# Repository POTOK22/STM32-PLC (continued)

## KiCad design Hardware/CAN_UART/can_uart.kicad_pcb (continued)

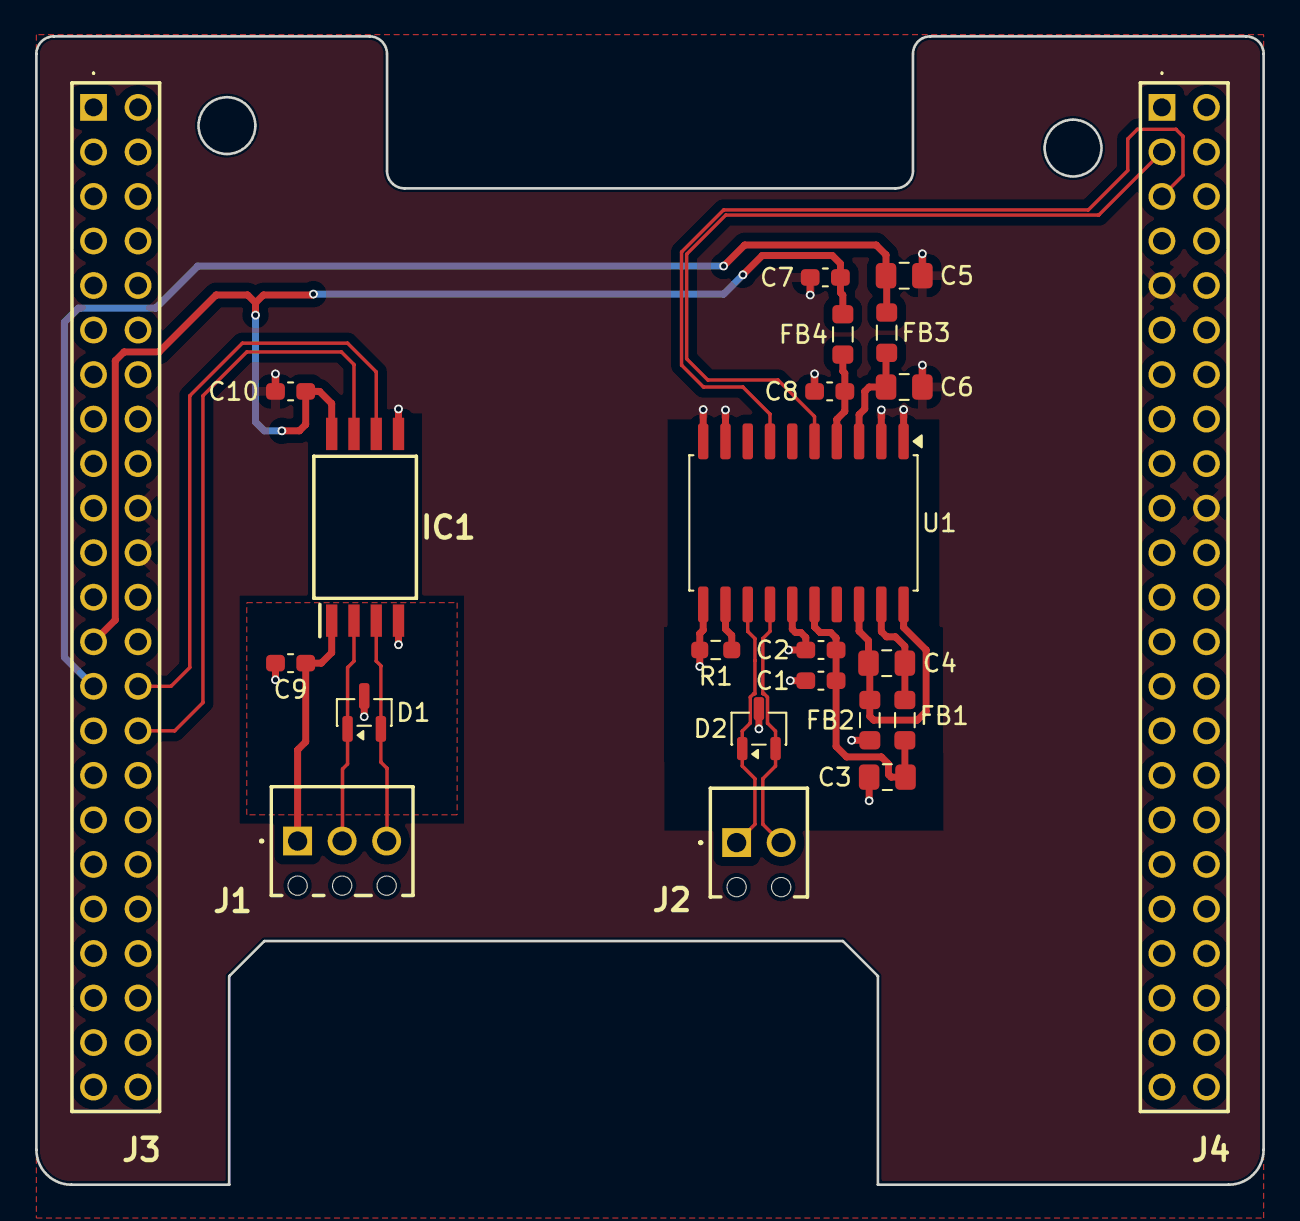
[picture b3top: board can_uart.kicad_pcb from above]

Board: 4 copper layers, 70.0 x 65.5 mm, 23 parts (0 on the bottom side), 20 nets.

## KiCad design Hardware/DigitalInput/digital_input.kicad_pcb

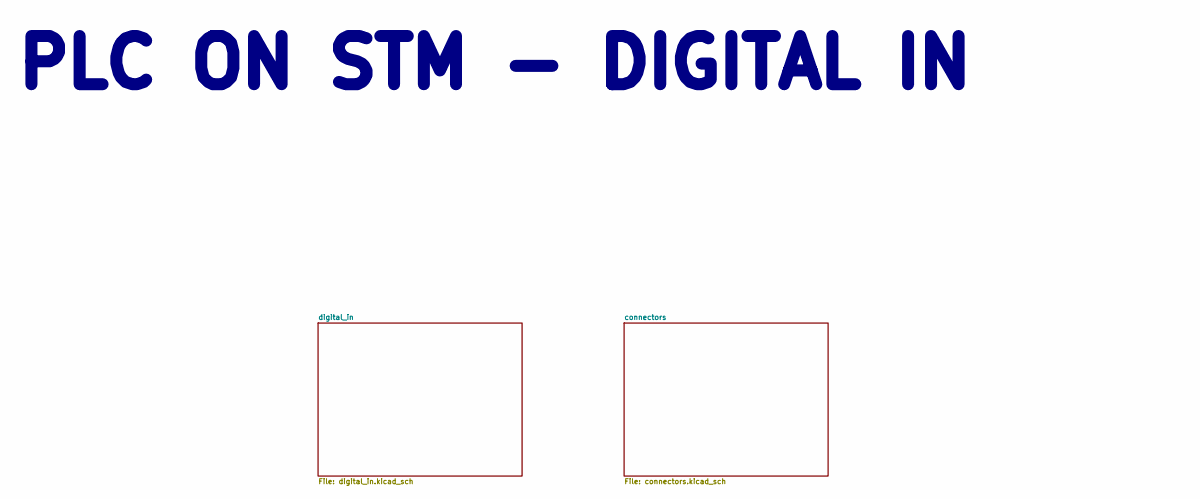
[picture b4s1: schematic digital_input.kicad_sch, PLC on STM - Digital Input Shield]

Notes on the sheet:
PLC ON STM - DIGITAL IN

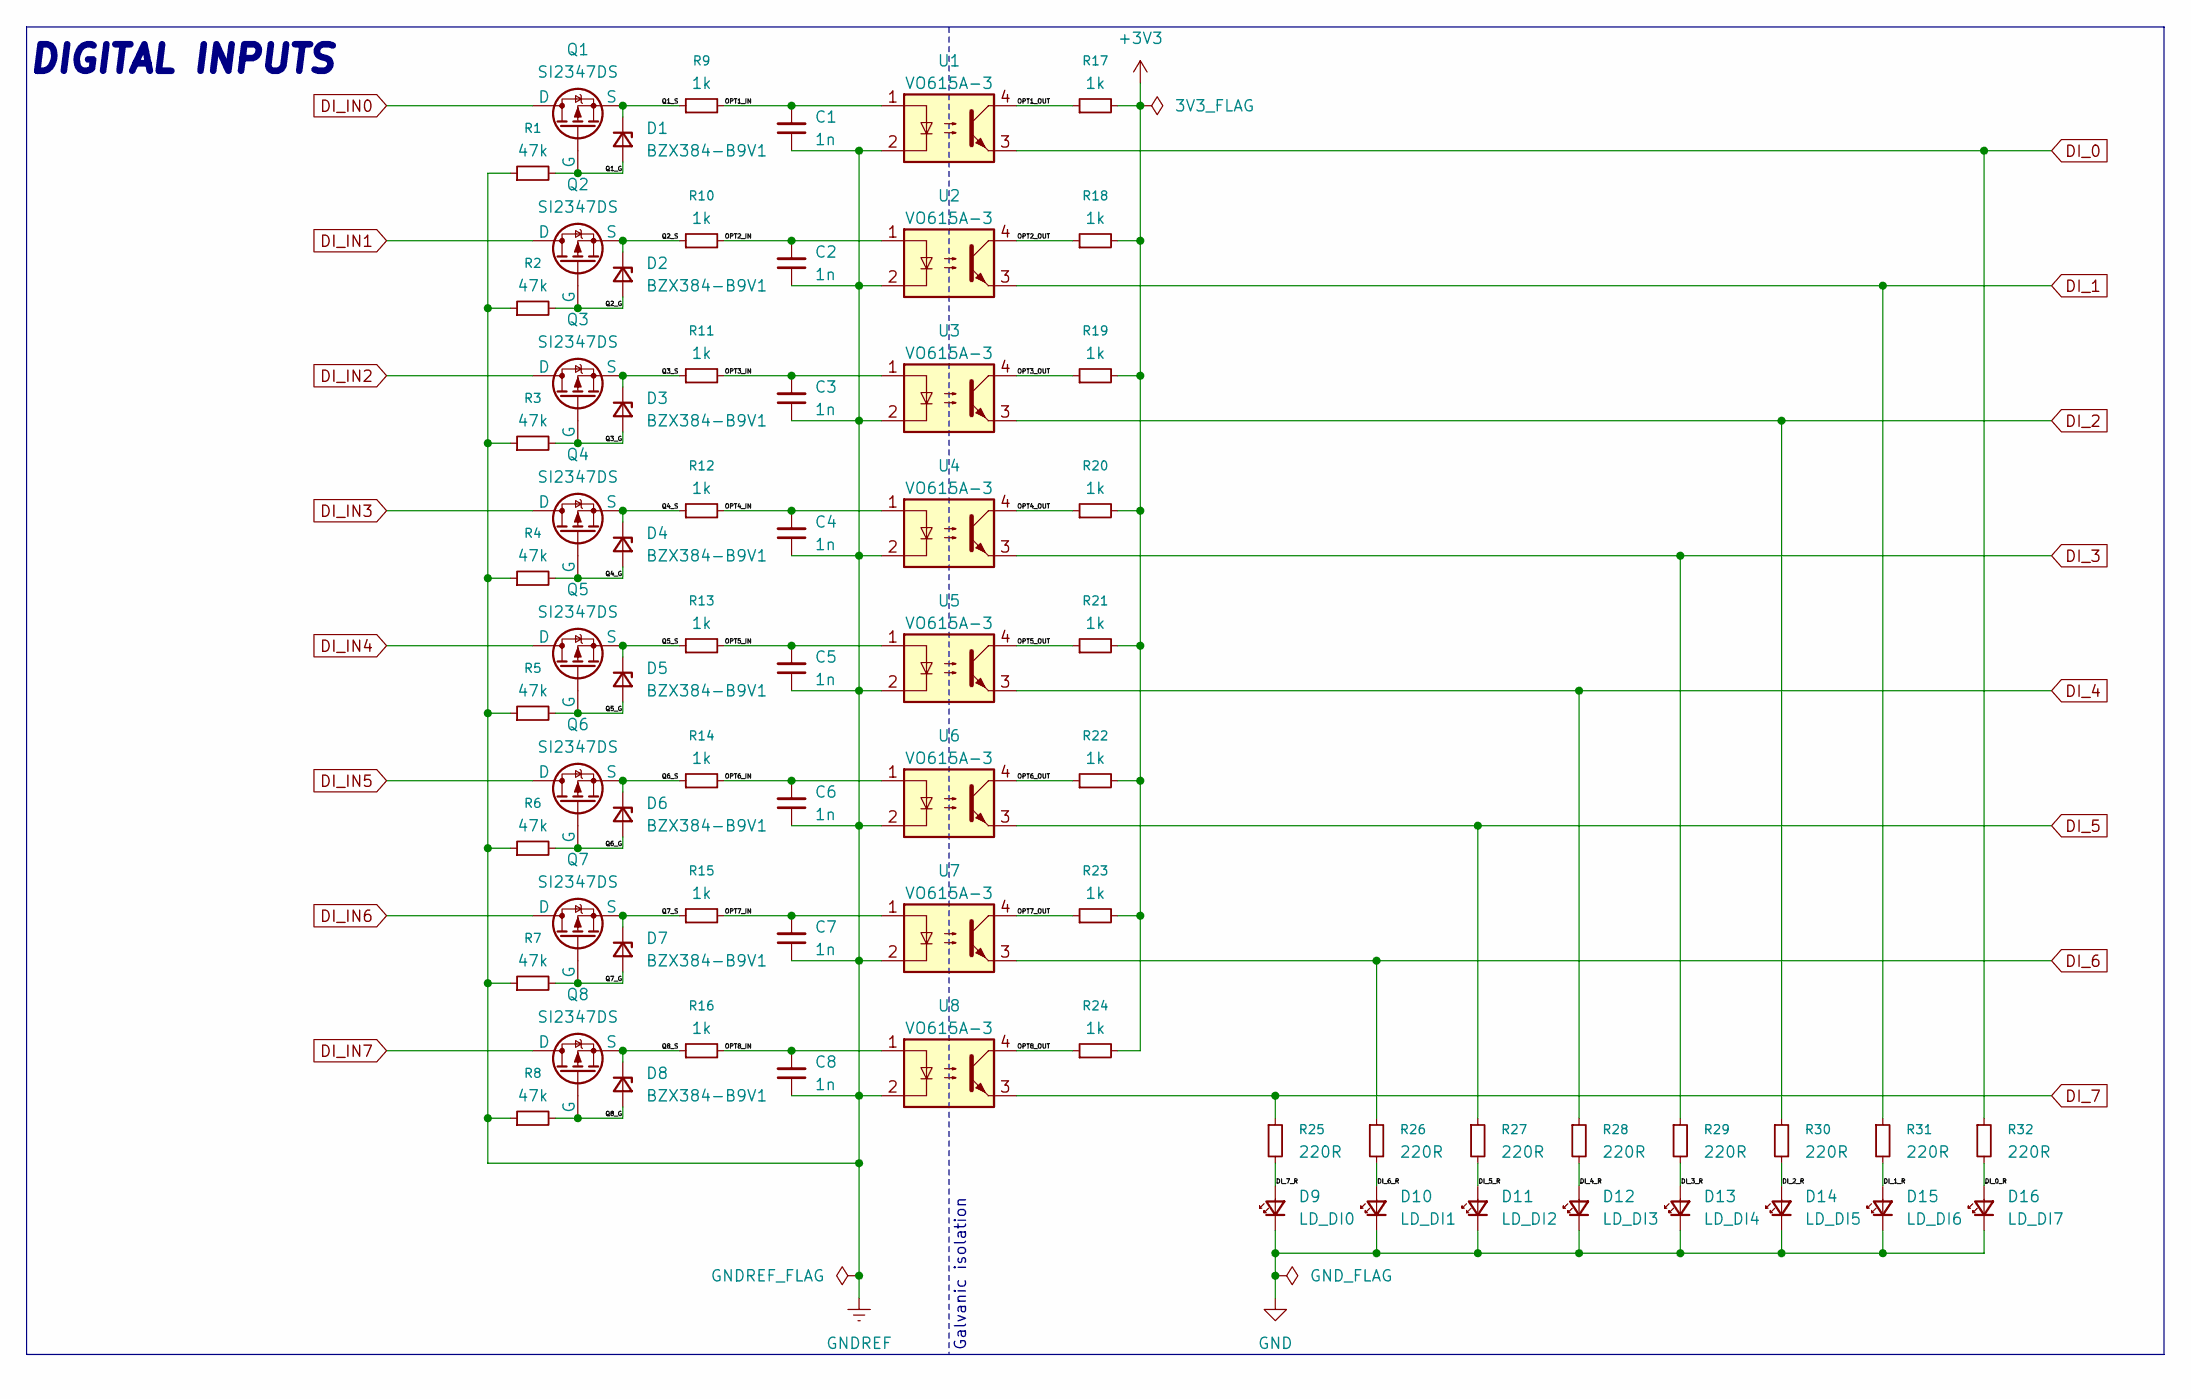
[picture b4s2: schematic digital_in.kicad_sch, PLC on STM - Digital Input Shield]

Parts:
C1, C2, C3, C4, C5, C6, C7, C8: 1n; C_0603_1608Metric_Pad1.08x0.95mm_HandSolder; Mouser Part Number 81-GRT1885C1E102JA2D
D1, D2, D3, D4, D5, D6, D7, D8: BZX384-B9V1; D_SOD-323_HandSoldering; Mouser Part Number 771-BZX384-B9V1-T/R
D9: LD_DI0; LED_0603_1608Metric_Pad1.05x0.95mm_HandSolder
D10: LD_DI1; LED_0603_1608Metric_Pad1.05x0.95mm_HandSolder
D11: LD_DI2; LED_0603_1608Metric_Pad1.05x0.95mm_HandSolder
D12: LD_DI3; LED_0603_1608Metric_Pad1.05x0.95mm_HandSolder
D13: LD_DI4; LED_0603_1608Metric_Pad1.05x0.95mm_HandSolder
D14: LD_DI5; LED_0603_1608Metric_Pad1.05x0.95mm_HandSolder
D15: LD_DI6; LED_0603_1608Metric_Pad1.05x0.95mm_HandSolder
D16: LD_DI7; LED_0603_1608Metric_Pad1.05x0.95mm_HandSolder
Q1, Q2, Q3, Q4, Q5, Q6, Q7, Q8: SI2347DS; SOT-23-3; Mouser Part Number 78-SI2347DS-T1-GE3
R1, R2, R3, R4, R5, R6, R7, R8: 47k; R_0603_1608Metric_Pad0.98x0.95mm_HandSolder; Mouser Part Number 71-CRCW0603-47K-E3
R9, R10, R11, R12, R13, R14, R15, R16, R17, R18, R19, R20, R21, R22, R23, R24: 1k; R_0603_1608Metric_Pad0.98x0.95mm_HandSolder; Mouser Part Number 71-CRCW06031K00FKED
R25, R26, R27, R28, R29, R30, R31, R32: 220R; R_0603_1608Metric_Pad0.98x0.95mm_HandSolder; Mouser Part Number 71-CRCW0603220RFKEAH
U1, U2, U3, U4, U5, U6, U7, U8: VO615A-3; DIP-4_W8.89mm_SMDSocket_LongPads

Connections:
+3V3: R17.2, R18.2, R19.2, R20.2, R21.2, R22.2, R23.2, R24.2; also elsewhere on the board
/digital_in/DI_0_R: D16.2 (A), R32.2
/digital_in/DI_1_R: D15.2 (A), R31.2
/digital_in/DI_2_R: D14.2 (A), R30.2
/digital_in/DI_3_R: D13.2 (A), R29.2
/digital_in/DI_4_R: D12.2 (A), R28.2
/digital_in/DI_5_R: D11.2 (A), R27.2
/digital_in/DI_6_R: D10.2 (A), R26.2
/digital_in/DI_7_R: D9.2 (A), R25.2
/digital_in/OPT1_IN: C1.2, R9.2, U1.1
/digital_in/OPT1_OUT: R17.1, U1.4
/digital_in/OPT2_IN: C2.2, R10.2, U2.1
/digital_in/OPT2_OUT: R18.1, U2.4
/digital_in/OPT3_IN: C3.2, R11.2, U3.1
/digital_in/OPT3_OUT: R19.1, U3.4
/digital_in/OPT4_IN: C4.2, R12.2, U4.1
/digital_in/OPT4_OUT: R20.1, U4.4
/digital_in/OPT5_IN: C5.2, R13.2, U5.1
/digital_in/OPT5_OUT: R21.1, U5.4
/digital_in/OPT6_IN: C6.2, R14.2, U6.1
/digital_in/OPT6_OUT: R22.1, U6.4
/digital_in/OPT7_IN: C7.2, R15.2, U7.1
/digital_in/OPT7_OUT: R23.1, U7.4
/digital_in/OPT8_IN: C8.2, R16.2, U8.1
/digital_in/OPT8_OUT: R24.1, U8.4
/digital_in/Q1_G: D1.2 (A), Q1.2 (G), R1.2
/digital_in/Q1_S: D1.1 (K), Q1.3 (S), R9.1
/digital_in/Q2_G: D2.2 (A), Q2.2 (G), R2.2
/digital_in/Q2_S: D2.1 (K), Q2.3 (S), R10.1
/digital_in/Q3_G: D3.2 (A), Q3.2 (G), R3.2
/digital_in/Q3_S: D3.1 (K), Q3.3 (S), R11.1
/digital_in/Q4_G: D4.2 (A), Q4.2 (G), R4.2
/digital_in/Q4_S: D4.1 (K), Q4.3 (S), R12.1
/digital_in/Q5_G: D5.2 (A), Q5.2 (G), R5.2
/digital_in/Q5_S: D5.1 (K), Q5.3 (S), R13.1
/digital_in/Q6_G: D6.2 (A), Q6.2 (G), R6.2
/digital_in/Q6_S: D6.1 (K), Q6.3 (S), R14.1
/digital_in/Q7_G: D7.2 (A), Q7.2 (G), R7.2
/digital_in/Q7_S: D7.1 (K), Q7.3 (S), R15.1
/digital_in/Q8_G: D8.2 (A), Q8.2 (G), R8.2
/digital_in/Q8_S: D8.1 (K), Q8.3 (S), R16.1
DI_0: R32.1, U1.3; also elsewhere on the board
DI_1: R31.1, U2.3; also elsewhere on the board
DI_2: R30.1, U3.3; also elsewhere on the board
DI_3: R29.1, U4.3; also elsewhere on the board
DI_4: R28.1, U5.3; also elsewhere on the board
DI_5: R27.1, U6.3; also elsewhere on the board
DI_6: R26.1, U7.3; also elsewhere on the board
DI_7: R25.1, U8.3; also elsewhere on the board
DI_IN0: Q1.1 (D); also elsewhere on the board
DI_IN1: Q2.1 (D); also elsewhere on the board
DI_IN2: Q3.1 (D); also elsewhere on the board
DI_IN3: Q4.1 (D); also elsewhere on the board
DI_IN4: Q5.1 (D); also elsewhere on the board
DI_IN5: Q6.1 (D); also elsewhere on the board
DI_IN6: Q7.1 (D); also elsewhere on the board
DI_IN7: Q8.1 (D); also elsewhere on the board
GND: D9.1 (K), D10.1 (K), D11.1 (K), D12.1 (K), D13.1 (K), D14.1 (K), D15.1 (K), D16.1 (K); also elsewhere on the board
GNDREF: C1.1, C2.1, C3.1, C4.1, C5.1, C6.1, C7.1, C8.1, R1.1, R2.1, R3.1, R4.1, R5.1, R6.1, R7.1, R8.1, U1.2, U2.2, U3.2, U4.2, U5.2, U6.2, U7.2, U8.2; also elsewhere on the board

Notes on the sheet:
DIGITAL INPUTS
Galvanic isolation

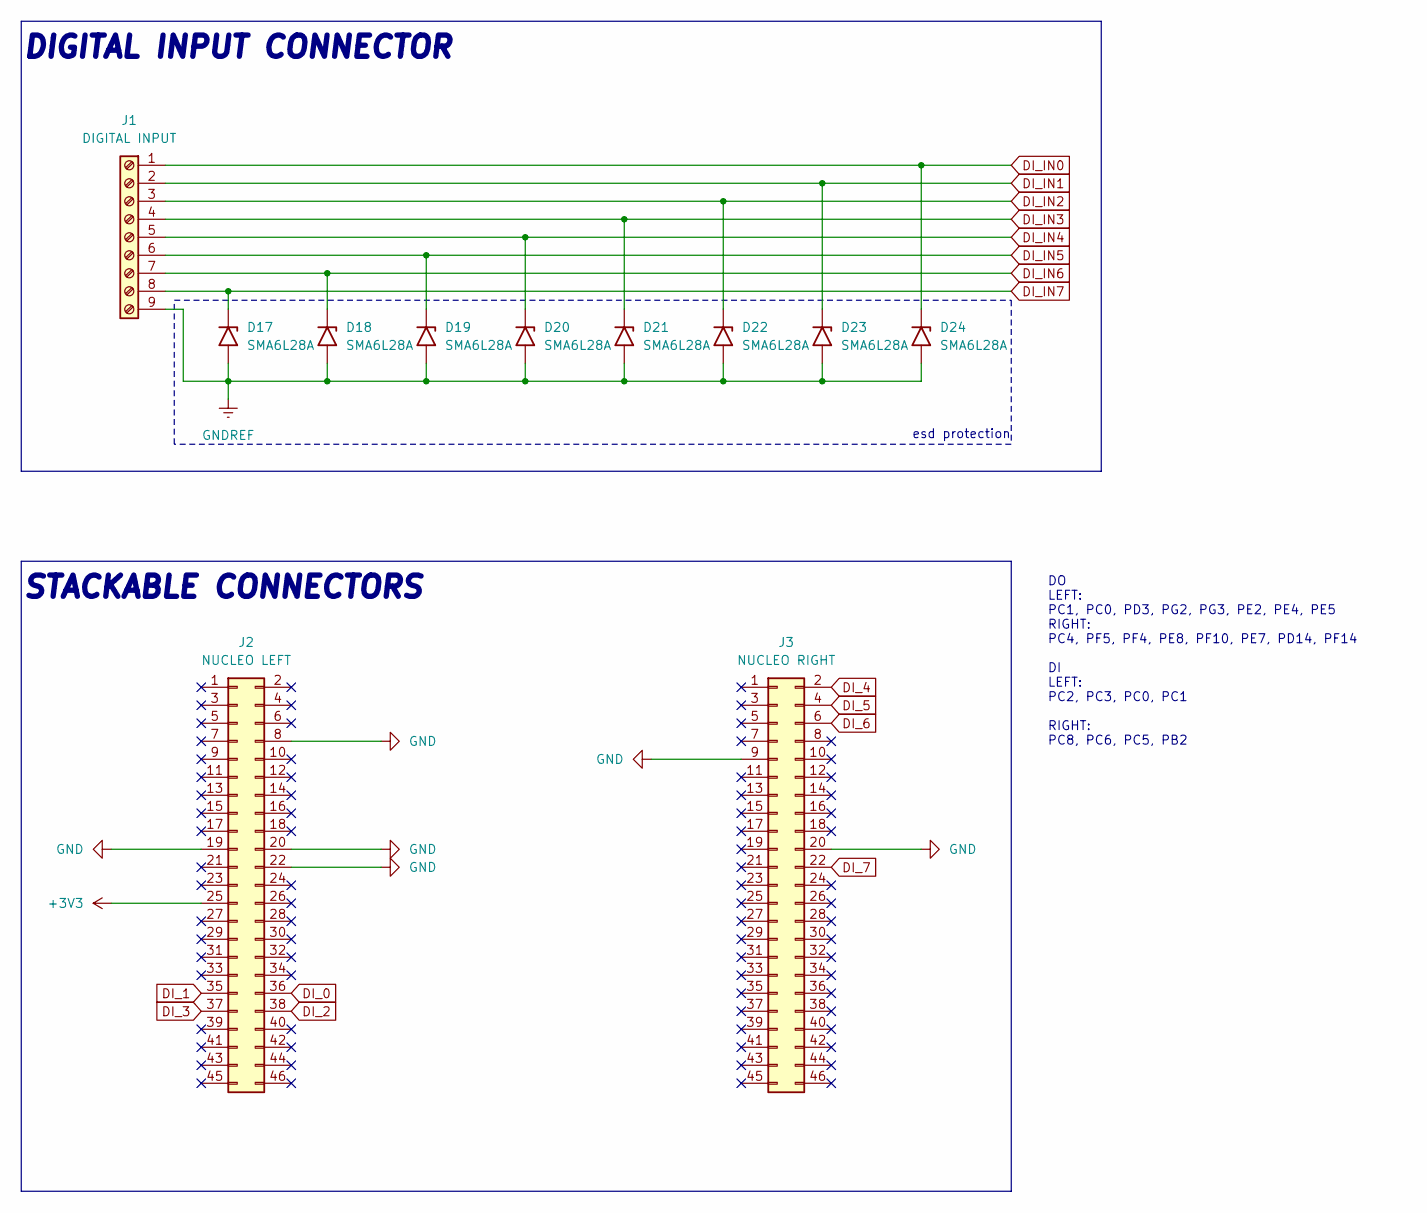
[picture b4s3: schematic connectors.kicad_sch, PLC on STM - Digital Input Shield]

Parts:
D17, D18, D19, D20, D21, D22, D23, D24: SMA6L28A; D_SMA; Mouser Part Number 576-SMA6L28A
J1: DIGITAL INPUT; 1725724; Mouser Part Number 651-1725724
J2: NUCLEO LEFT; PRT12790; Mouser Part Number 474-PRT-12790
J3: NUCLEO RIGHT; PRT12790; Mouser Part Number 474-PRT-12790

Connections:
+3V3: J2.25; also elsewhere on the board
DI_0: J2.36; also elsewhere on the board
DI_1: J2.35; also elsewhere on the board
DI_2: J2.38; also elsewhere on the board
DI_3: J2.37; also elsewhere on the board
DI_4: J3.2; also elsewhere on the board
DI_5: J3.4; also elsewhere on the board
DI_6: J3.6; also elsewhere on the board
DI_7: J3.22; also elsewhere on the board
DI_IN0: D24.1 (A1), J1.1; also elsewhere on the board
DI_IN1: D23.1 (A1), J1.2; also elsewhere on the board
DI_IN2: D22.1 (A1), J1.3; also elsewhere on the board
DI_IN3: D21.1 (A1), J1.4; also elsewhere on the board
DI_IN4: D20.1 (A1), J1.5; also elsewhere on the board
DI_IN5: D19.1 (A1), J1.6; also elsewhere on the board
DI_IN6: D18.1 (A1), J1.7; also elsewhere on the board
DI_IN7: D17.1 (A1), J1.8; also elsewhere on the board
GND: J2.8, J2.19, J2.20, J2.22, J3.9, J3.20; also elsewhere on the board
GNDREF: D17.2 (A2), D18.2 (A2), D19.2 (A2), D20.2 (A2), D21.2 (A2), D22.2 (A2), D23.2 (A2), D24.2 (A2), J1.9; also elsewhere on the board

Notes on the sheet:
STACKABLE CONNECTORS
DIGITAL INPUT CONNECTOR
esd protection
DO LEFT: PC1, PC0, PD3, PG2, PG3, PE2, PE4, PE5 RIGHT: PC4, PF5, PF4, PE8, PF10, PE7, PD14, PF14 DI LEFT: PC2, PC3, PC0, PC1 RIGHT: PC8, PC6, PC5, PB2

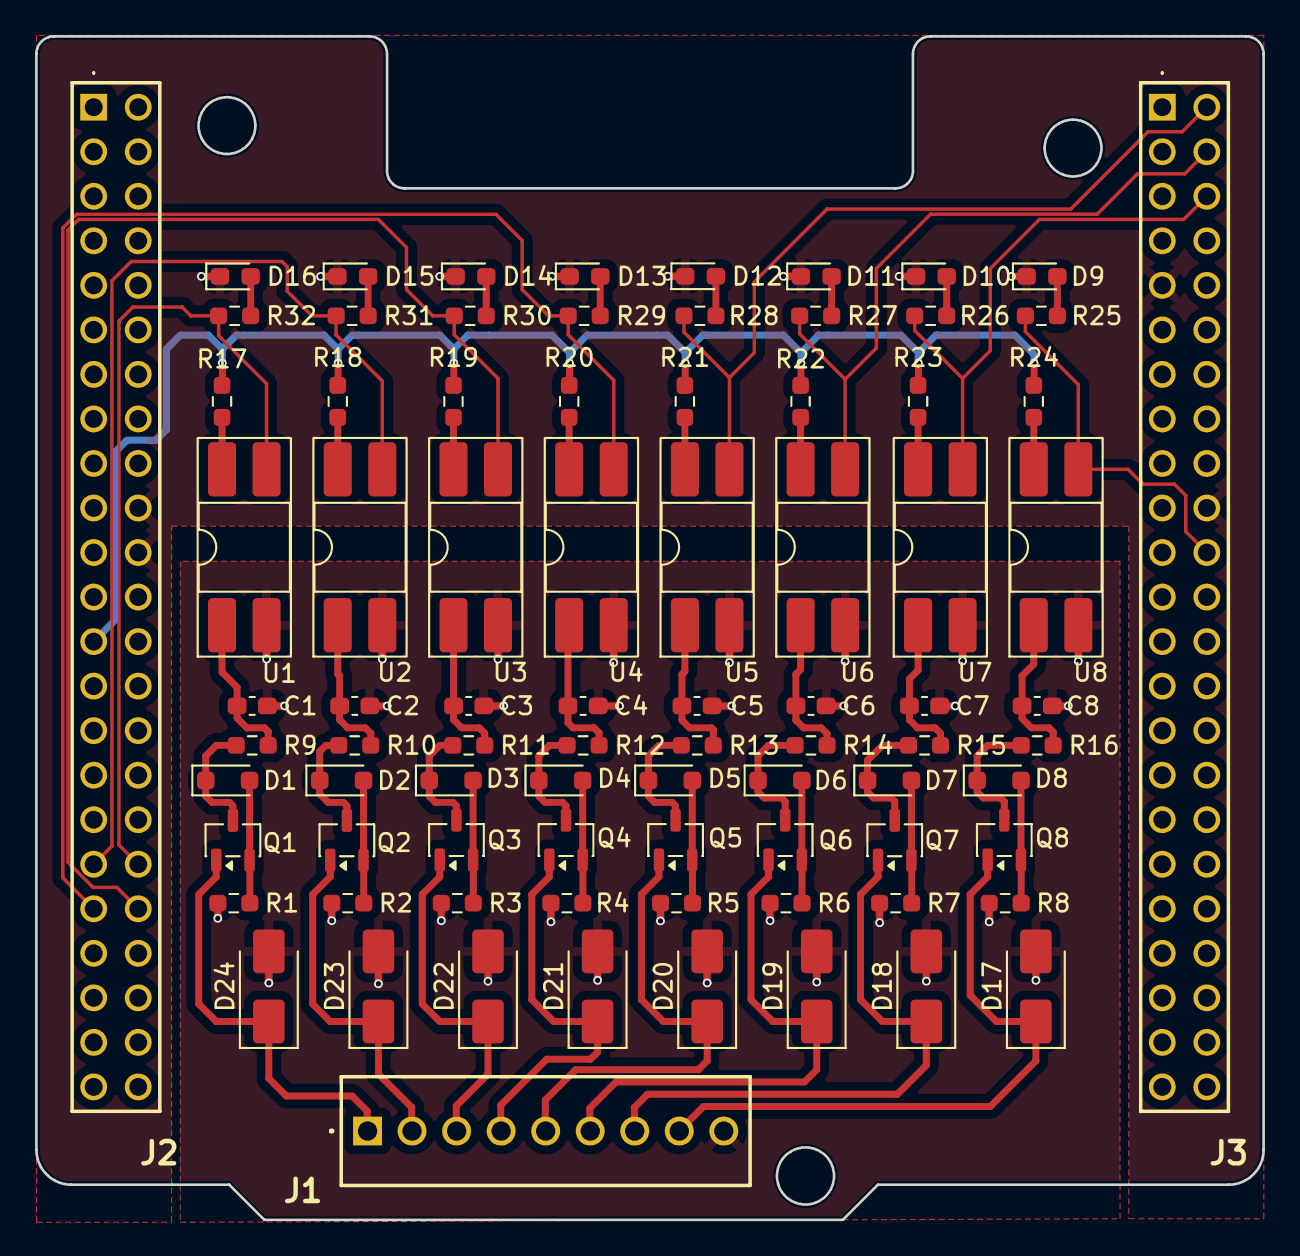
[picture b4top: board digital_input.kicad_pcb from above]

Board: 4 copper layers, 70.0 x 67.5 mm, 83 parts (0 on the bottom side), 59 nets.

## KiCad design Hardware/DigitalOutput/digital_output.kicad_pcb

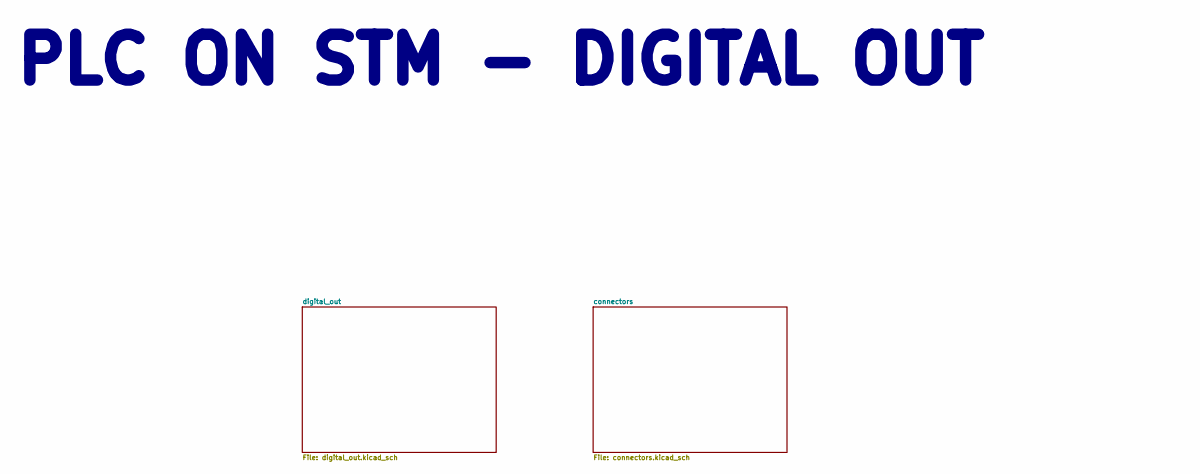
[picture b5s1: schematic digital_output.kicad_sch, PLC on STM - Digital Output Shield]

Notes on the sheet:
PLC ON STM - DIGITAL OUT

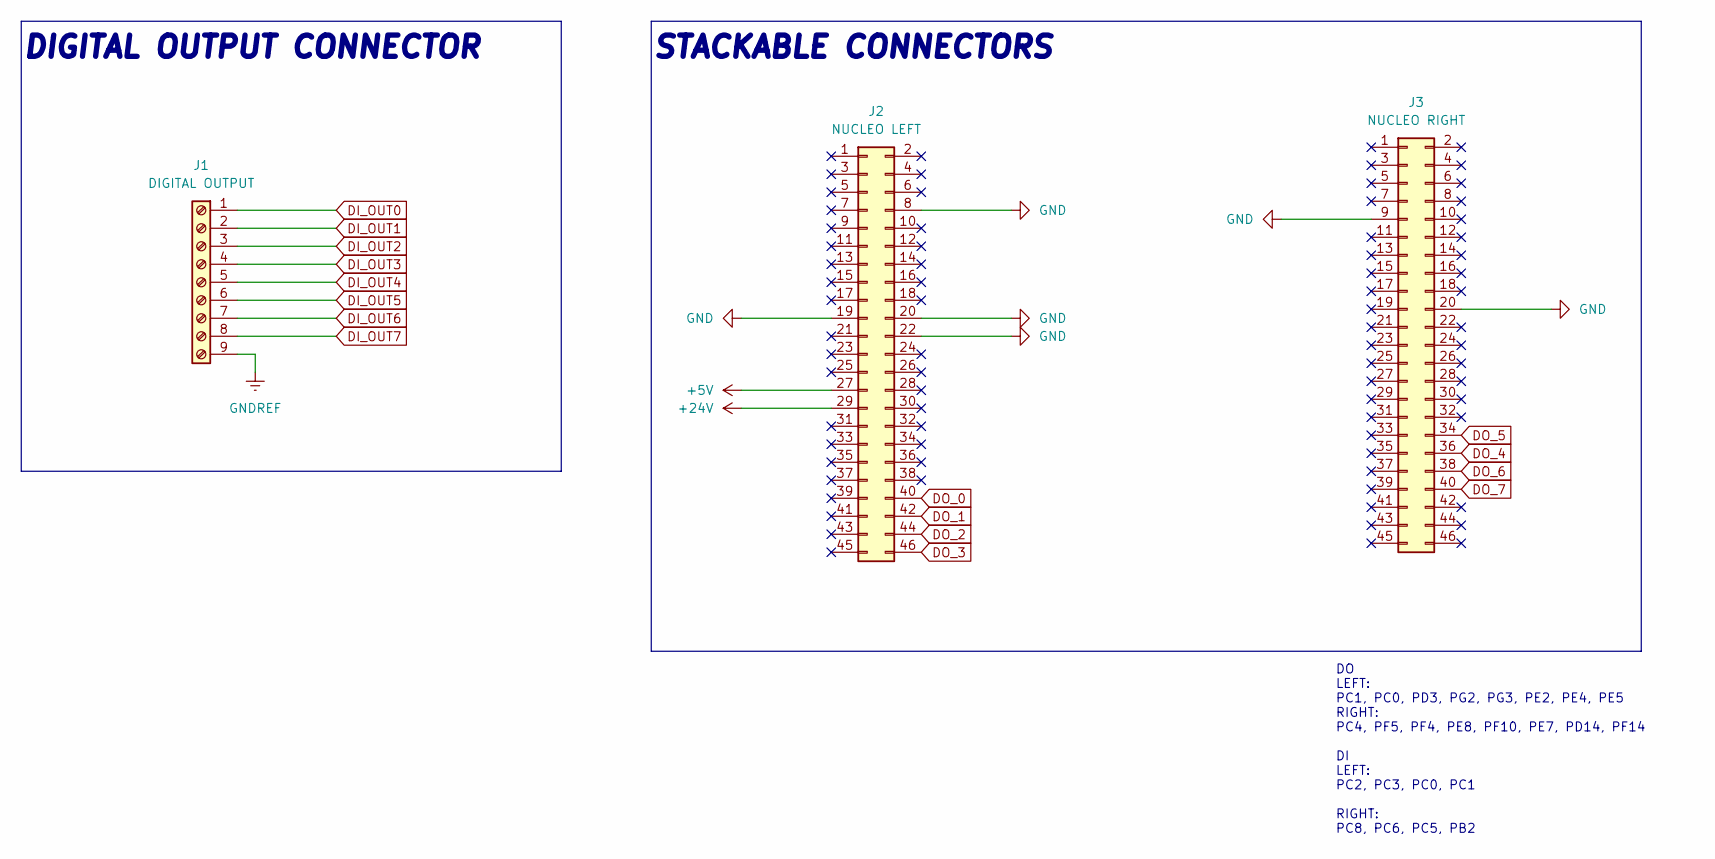
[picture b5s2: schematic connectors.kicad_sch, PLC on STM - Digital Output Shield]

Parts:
J1: DIGITAL OUTPUT; 1725724; Mouser Part Number 651-1725724
J2: NUCLEO LEFT; PRT12790; Mouser Part Number 474-PRT-12790
J3: NUCLEO RIGHT; PRT12790; Mouser Part Number 474-PRT-12790

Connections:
+5V: J2.27; also elsewhere on the board
+24V: J2.29; also elsewhere on the board
DI_OUT0: J1.1; also elsewhere on the board
DI_OUT1: J1.2; also elsewhere on the board
DI_OUT2: J1.3; also elsewhere on the board
DI_OUT3: J1.4; also elsewhere on the board
DI_OUT4: J1.5; also elsewhere on the board
DI_OUT5: J1.6; also elsewhere on the board
DI_OUT6: J1.7; also elsewhere on the board
DI_OUT7: J1.8; also elsewhere on the board
DO_0: J2.40; also elsewhere on the board
DO_1: J2.42; also elsewhere on the board
DO_2: J2.44; also elsewhere on the board
DO_3: J2.46; also elsewhere on the board
DO_4: J3.36; also elsewhere on the board
DO_5: J3.34; also elsewhere on the board
DO_6: J3.38; also elsewhere on the board
DO_7: J3.40; also elsewhere on the board
GND: J2.8, J2.19, J2.20, J2.22, J3.9, J3.20; also elsewhere on the board
GNDREF: J1.9; also elsewhere on the board

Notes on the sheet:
DO LEFT: PC1, PC0, PD3, PG2, PG3, PE2, PE4, PE5 RIGHT: PC4, PF5, PF4, PE8, PF10, PE7, PD14, PF14 DI LEFT: PC2, PC3, PC0, PC1 RIGHT: PC8, PC6, PC5, PB2
DIGITAL OUTPUT CONNECTOR
STACKABLE CONNECTORS

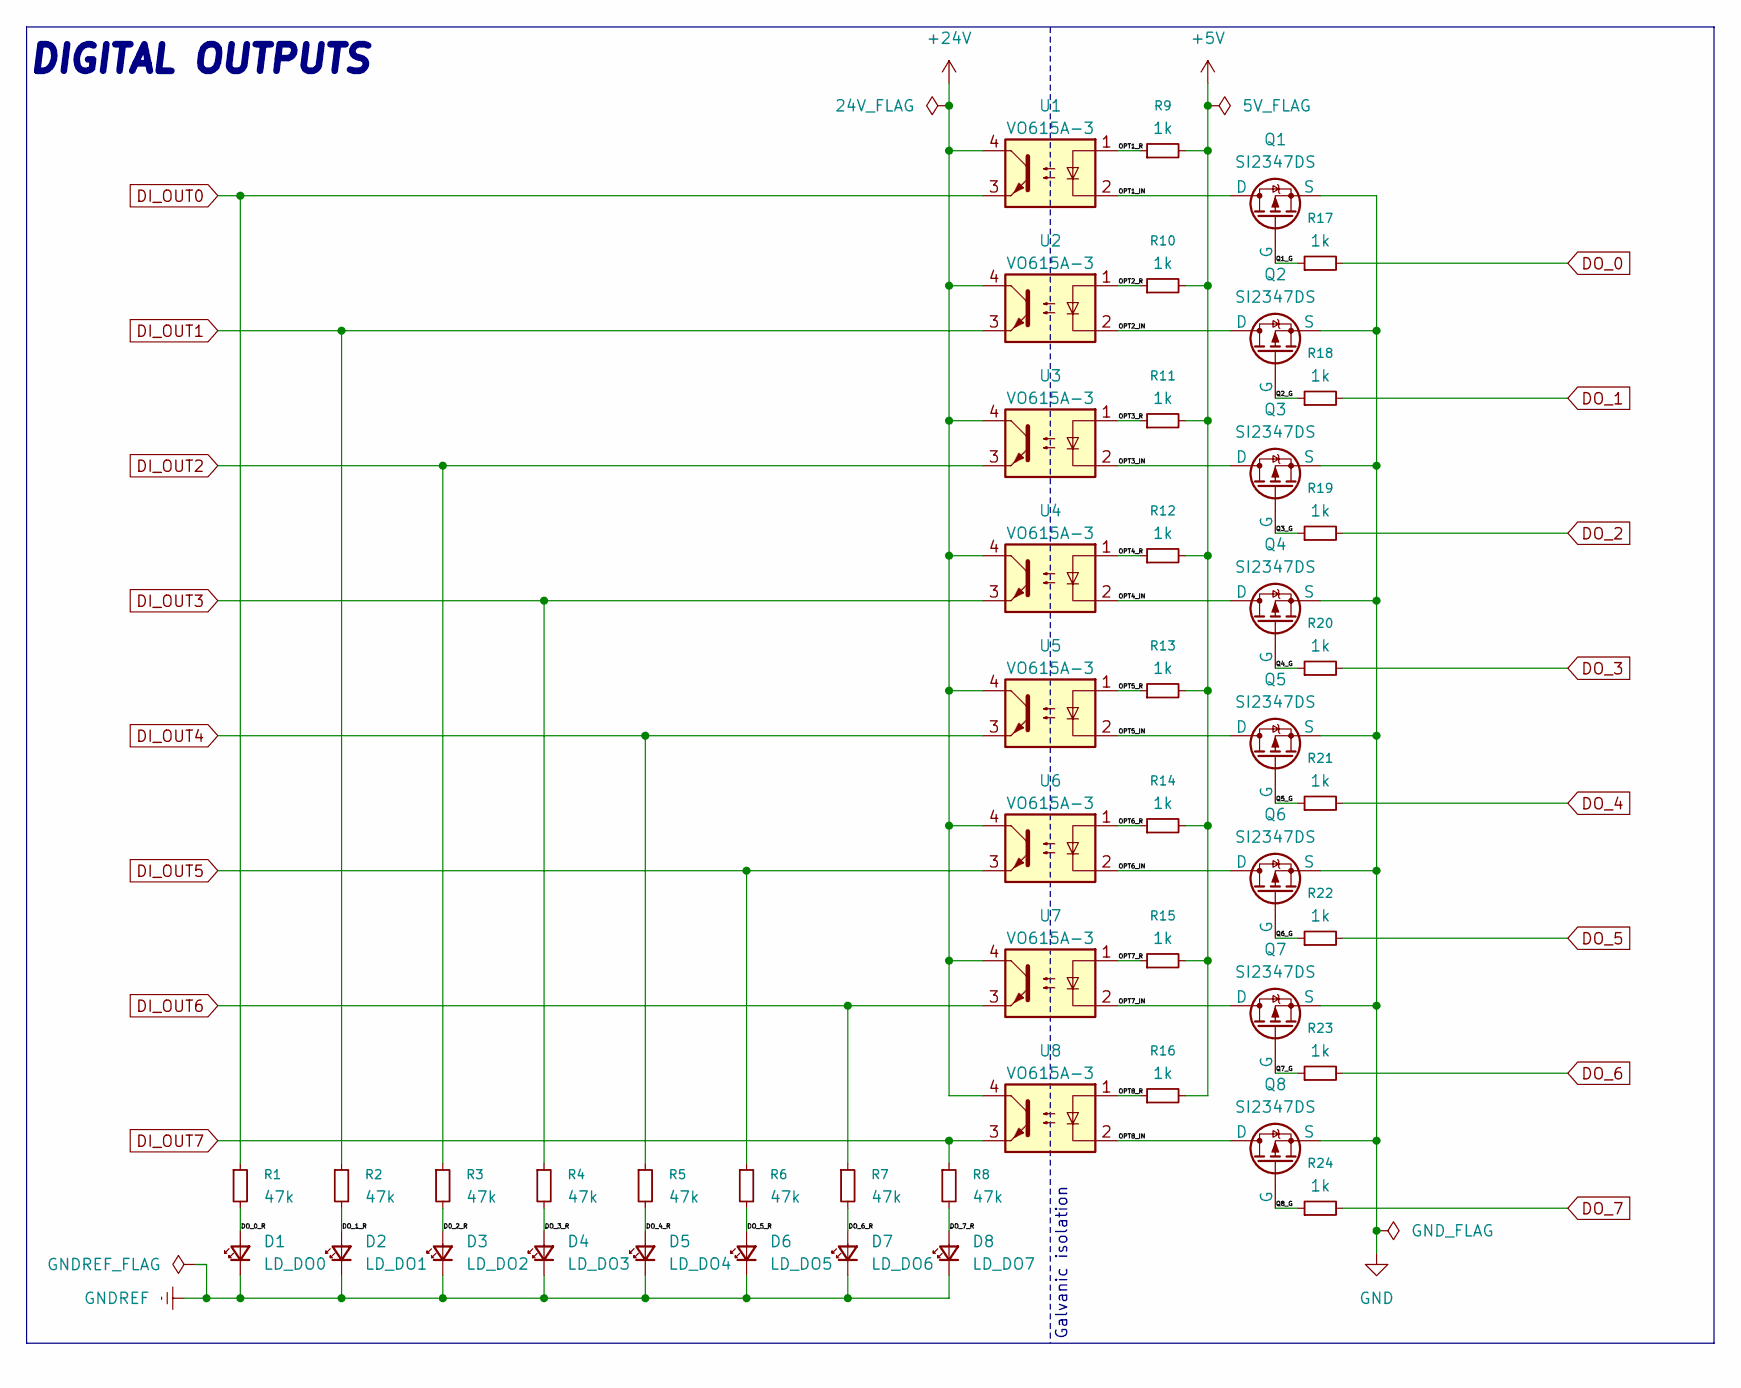
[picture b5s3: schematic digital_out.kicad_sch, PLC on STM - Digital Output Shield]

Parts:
D1: LD_DO0; LED_0603_1608Metric_Pad1.05x0.95mm_HandSolder
D2: LD_DO1; LED_0603_1608Metric_Pad1.05x0.95mm_HandSolder
D3: LD_DO2; LED_0603_1608Metric_Pad1.05x0.95mm_HandSolder
D4: LD_DO3; LED_0603_1608Metric_Pad1.05x0.95mm_HandSolder
D5: LD_DO4; LED_0603_1608Metric_Pad1.05x0.95mm_HandSolder
D6: LD_DO5; LED_0603_1608Metric_Pad1.05x0.95mm_HandSolder
D7: LD_DO6; LED_0603_1608Metric_Pad1.05x0.95mm_HandSolder
D8: LD_DO7; LED_0603_1608Metric_Pad1.05x0.95mm_HandSolder
Q1, Q2, Q3, Q4, Q5, Q6, Q7, Q8: SI2347DS; SOT-23-3; Mouser Part Number 78-SI2347DS-T1-GE3
R1, R2, R3, R4, R5, R6, R7, R8: 47k; R_0603_1608Metric_Pad0.98x0.95mm_HandSolder; Mouser Part Number 71-CRCW0603-47K-E3
R9, R10, R11, R12, R13, R14, R15, R16, R17, R18, R19, R20, R21, R22, R23, R24: 1k; R_0603_1608Metric_Pad0.98x0.95mm_HandSolder; Mouser Part Number 71-CRCW06031K00FKED
U1, U2, U3, U4, U5, U6, U7, U8: VO615A-3; DIP-4_W8.89mm_SMDSocket_LongPads

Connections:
+5V: R9.2, R10.2, R11.2, R12.2, R13.2, R14.2, R15.2, R16.2; also elsewhere on the board
+24V: U1.4, U2.4, U3.4, U4.4, U5.4, U6.4, U7.4, U8.4; also elsewhere on the board
/digital_out/D0_2_R: D3.2 (A), R3.2
/digital_out/DO_0_R: D1.2 (A), R1.2
/digital_out/DO_1_R: D2.2 (A), R2.2
/digital_out/DO_3_R: D4.2 (A), R4.2
/digital_out/DO_4_R: D5.2 (A), R5.2
/digital_out/DO_5_R: D6.2 (A), R6.2
/digital_out/DO_6_R: D7.2 (A), R7.2
/digital_out/DO_7_R: D8.2 (A), R8.2
/digital_out/OPT1_IN: Q1.1 (D), U1.2
/digital_out/OPT1_R: R9.1, U1.1
/digital_out/OPT2_IN: Q2.1 (D), U2.2
/digital_out/OPT2_R: R10.1, U2.1
/digital_out/OPT3_IN: Q3.1 (D), U3.2
/digital_out/OPT3_R: R11.1, U3.1
/digital_out/OPT4_IN: Q4.1 (D), U4.2
/digital_out/OPT4_R: R12.1, U4.1
/digital_out/OPT5_IN: Q5.1 (D), U5.2
/digital_out/OPT5_R: R13.1, U5.1
/digital_out/OPT6_IN: Q6.1 (D), U6.2
/digital_out/OPT6_R: R14.1, U6.1
/digital_out/OPT7_IN: Q7.1 (D), U7.2
/digital_out/OPT7_R: R15.1, U7.1
/digital_out/OPT8_IN: Q8.1 (D), U8.2
/digital_out/OPT8_R: R16.1, U8.1
/digital_out/Q1_G: Q1.2 (G), R17.1
/digital_out/Q2_G: Q2.2 (G), R18.1
/digital_out/Q3_G: Q3.2 (G), R19.1
/digital_out/Q4_G: Q4.2 (G), R20.1
/digital_out/Q5_G: Q5.2 (G), R21.1
/digital_out/Q6_G: Q6.2 (G), R22.1
/digital_out/Q7_G: Q7.2 (G), R23.1
/digital_out/Q8_G: Q8.2 (G), R24.1
DI_OUT0: R1.1, U1.3; also elsewhere on the board
DI_OUT1: R2.1, U2.3; also elsewhere on the board
DI_OUT2: R3.1, U3.3; also elsewhere on the board
DI_OUT3: R4.1, U4.3; also elsewhere on the board
DI_OUT4: R5.1, U5.3; also elsewhere on the board
DI_OUT5: R6.1, U6.3; also elsewhere on the board
DI_OUT6: R7.1, U7.3; also elsewhere on the board
DI_OUT7: R8.1, U8.3; also elsewhere on the board
DO_0: R17.2; also elsewhere on the board
DO_1: R18.2; also elsewhere on the board
DO_2: R19.2; also elsewhere on the board
DO_3: R20.2; also elsewhere on the board
DO_4: R21.2; also elsewhere on the board
DO_5: R22.2; also elsewhere on the board
DO_6: R23.2; also elsewhere on the board
DO_7: R24.2; also elsewhere on the board
GND: Q1.3 (S), Q2.3 (S), Q3.3 (S), Q4.3 (S), Q5.3 (S), Q6.3 (S), Q7.3 (S), Q8.3 (S); also elsewhere on the board
GNDREF: D1.1 (K), D2.1 (K), D3.1 (K), D4.1 (K), D5.1 (K), D6.1 (K), D7.1 (K), D8.1 (K); also elsewhere on the board

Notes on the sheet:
Galvanic isolation
DIGITAL OUTPUTS

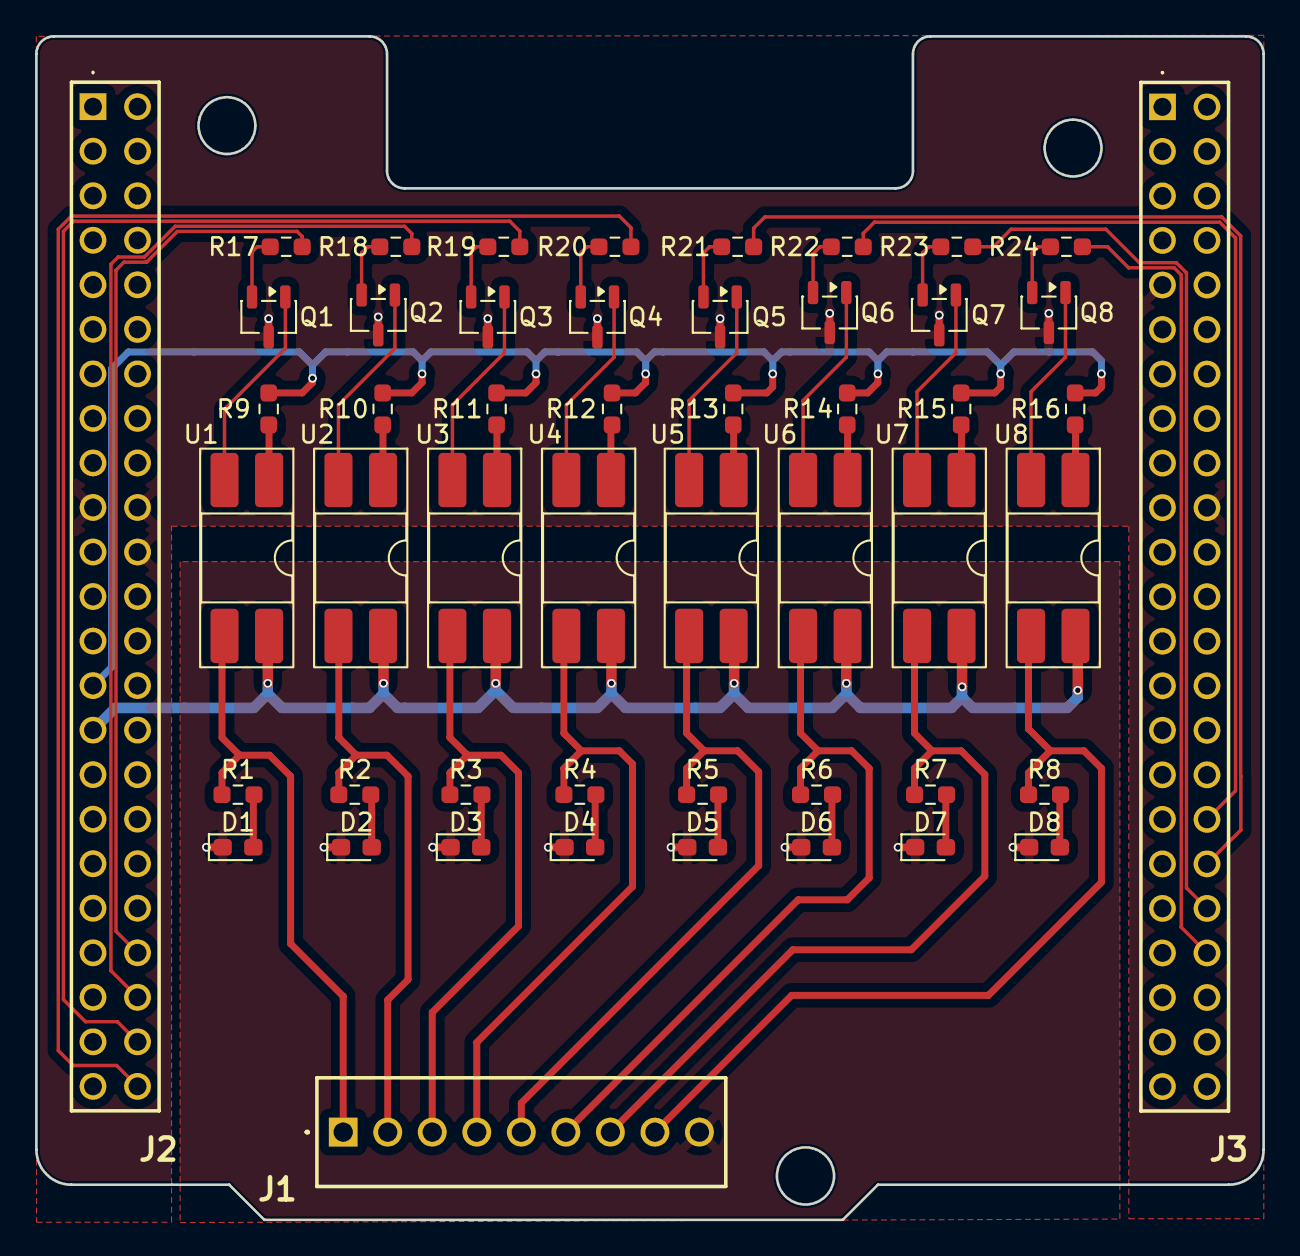
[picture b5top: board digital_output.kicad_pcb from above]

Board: 4 copper layers, 70.0 x 67.5 mm, 51 parts (0 on the bottom side), 52 nets.

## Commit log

2025-11-18 overcurrent protection idea added
2025-11-18 schematic added
2025-11-27 scheme update
2025-11-27 documentation update - new scheme
2025-12-26 schematic update
2025-12-27 hardware update - module shield division
2025-12-27 .gitignore update
2025-12-28 schematic update - all pcbs
2025-12-29 schematic update - digital and analog footprints added
2026-01-05 schematic update & pcb update
2026-01-09 digital output & digital input update
2026-01-10 digital input finished
2026-01-11 digital input pins update
2026-01-11 digital input update
2026-01-12 digital output & power finished
2026-01-13 analog & can finished
2026-01-13 small adjustments and final revision
2026-01-13 gerber files added
2026-01-14 small adjustments
